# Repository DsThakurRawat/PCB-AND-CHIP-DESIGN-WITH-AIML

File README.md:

# PCB-AI: Autonomous AI-Assisted Electronics & KiCad Engineering System

An end-to-end open-source pipeline for programmatic circuit synthesis, schematic capture, SPICE simulation, PCB layout, automated routing, and manufacturing exports using **KiCad 9**, **ngspice**, **FreeRouting**, **InteractiveHtmlBom**, **OpenCode**, and **Antigravity**.

---

## 🚀 Architecture & Core Pipelines

```
                     ┌───────────────────────────────┐
                     │   Structured Circuit Spec     │
                     │         (JSON / AI)           │
                     └───────────────┬───────────────┘
                                     │
           ┌─────────────────────────┴─────────────────────────┐
           ▼                                                   ▼
┌───────────────────────┐                           ┌─────────────────────┐
│  SPICE Simulator      │                           │  Schematic Builder  │
│  (ngspice 45.2)       │                           │  (kicad_sch_api)    │
└──────────┬────────────┘                           └──────────┬──────────┘
           │                                                   │
           ▼ (AC / Transient Plots)                            ▼ (.kicad_sch)
┌───────────────────────┐                           ┌─────────────────────┐
│ Waveform Analysis     │                           │ Automated ERC Check │
│ (Bode / Transient)    │                           │ (0 Violations)      │
└───────────────────────┘                           └──────────┬──────────┘
                                                               │
                                                               ▼ (.kicad_pcb)
                                                    ┌─────────────────────┐
                                                    │   PCB Layout Engine │
                                                    │   (pcbnew Python)   │
                                                    └──────────┬──────────┘
                                                               │
           ┌───────────────────────────────────────────────────┴───────────────────────────────────────┐
           ▼                                                   ▼                                       ▼
┌───────────────────────┐                           ┌─────────────────────┐                 ┌─────────────────────┐
│  FreeRouting Engine   │                           │  DRC Validator      │                 │ Manufacturing Pack  │
│  (Java 25 + DSN/SES)  │                           │  (--exit-code)      │                 │ Gerbers, Drill, BOM │
└───────────────────────┘                           └─────────────────────┘                 └──────────┬──────────┘
                                                                                                       │
                                                    ┌──────────────────────────────────────────────────┴──────────┐
                                                    ▼                                                             ▼
                                     ┌─────────────────────────────┐                               ┌─────────────────────────────┐
                                     │  Interactive HTML BOM       │                               │  3D Raytrace Render         │
                                     │  (InteractiveHtmlBom)       │                               │  (Perspective + Shaders)    │
                                     └─────────────────────────────┘                               └─────────────────────────────┘
```

---

## 🛠️ Toolchain & Installed Components

| Tool | Version | Purpose |
| :--- | :---: | :--- |
| **KiCad Suite** | 9.0.8 | Headless CLI automation & interactive visual design |
| **pcbnew** | 9.0.8 bindings | Direct programmatic PCB inspection & manipulation |
| **ngspice** | 45.2 | Circuit simulation (AC Bode frequency sweeps, Transient, DC) |
| **OpenJDK** | 25.0.4.1 | Java runtime for automated routing engine |
| **FreeRouting** | 2.5.0 | Specctra DSN/SES automated trace router |
| **InteractiveHtmlBom** | Latest | Self-contained visual HTML BOM for prototype assembly |
| **kicad_sch_api** | 0.5.5 | Programmatic schematic generation and wiring |
| **shapely** | 2.2.0 | 2D computational geometry and board outline math |
| **OpenCode MCP** | Active | Paired with `opencode/glm-5.3-flash-free` |
| **Antigravity MCP** | Active | Configured with 80+ native KiCad tools in `mcp_config.json` |

---

## 📁 Repository Structure

```
PCBDESIGN/
├── pcb_engine/
│   ├── circuit_spec.py      # Pydantic schema for structured circuit definitions
│   ├── sch_builder.py       # Programmatic .kicad_sch generator & auto-wiring
│   ├── pcb_builder.py       # Programmatic .kicad_pcb layout & footprint generator
│   └── simulator.py         # ngspice AC/transient simulator & matplotlib plotter
│
├── scripts/
│   ├── validate_design.py   # Automated ERC & DRC runner (--exit-code-violations)
│   ├── generate_ibom.py     # Interactive HTML BOM generator
│   ├── render_3d.py         # Altium-style 3D raytrace renderer
│   ├── autoroute.py         # Standalone Freerouting CLI runner
│   ├── export_manufacturing.py # Complete Gerber, drill, pos, PDF, 3D, and iBOM packager
│   └── run_all_benchmarks.sh   # Master benchmark verification suite
│
├── reference_circuits/
│   ├── 01_ldo_power_supply/ # 3.3V Linear Voltage Regulator Module
│   │   ├── spec.json        # Circuit specification
│   │   ├── ldo_power_supply.kicad_sch
│   │   ├── ldo_power_supply.kicad_pcb
│   │   ├── simulation_transient.png
│   │   └── manufacturing/   # Gerbers ZIP, drill, pos CSV, PDF, ibom.html, 3d.png
│   │
│   └── 02_sallen_key_filter/# 2nd-Order Sallen-Key Active Low-Pass Filter (1 kHz)
│       ├── spec.json        # Circuit specification
│       ├── sallen_key_filter.kicad_sch
│       ├── sallen_key_filter.kicad_pcb
│       ├── simulation_bode.png
│       └── manufacturing/   # Gerbers ZIP, drill, pos CSV, PDF, ibom.html, 3d.png
│
├── ne555_led_blinker/        # Single-Layer Astable 1Hz LED Blinker (DIP-8, 48x36mm)
│   ├── spec.json            # Circuit definition
│   ├── ne555_led_blinker.kicad_sch
│   ├── ne555_led_blinker.kicad_pcb  # 100% single-layer routed on F.Cu (0 vias, 0 DRC violations)
│   ├── ne555_simulation_transient.png
│   └── manufacturing/       # Gerbers ZIP, drill, pos CSV, PDF, ibom.html, 3d.png
│
├── docs/
│   ├── ENGINEERING_RULES_AND_LESSONS.md # Complete rules, failure modes & decisions log
│   └── mcp_vs_scripting_benchmark.md    # KiCad MCP vs scripting comparison
│
├── demo_board/              # Test project used for live GUI tracking & MCP verification
└── README.md
```

---

## ⚡ Quick Start & Commands

### 1. Run Complete Benchmark Suite
```bash
./scripts/run_all_benchmarks.sh
```

### 2. Validate Any Schematic or Board
```bash
python3 scripts/validate_design.py --sch <path_to_sch> --pcb <path_to_pcb>
```

### 3. Generate Interactive HTML BOM
```bash
python3 scripts/generate_ibom.py <path_to_pcb> [output_dir]
```

### 4. Generate Altium-Style 3D Render
```bash
python3 scripts/render_3d.py <path_to_pcb> [output_image.png]
```

### 5. Package Complete Manufacturing Archive (Gerbers + Drill + iBOM + 3D)
```bash
python3 scripts/export_manufacturing.py <path_to_pcb> [output_dir]
```

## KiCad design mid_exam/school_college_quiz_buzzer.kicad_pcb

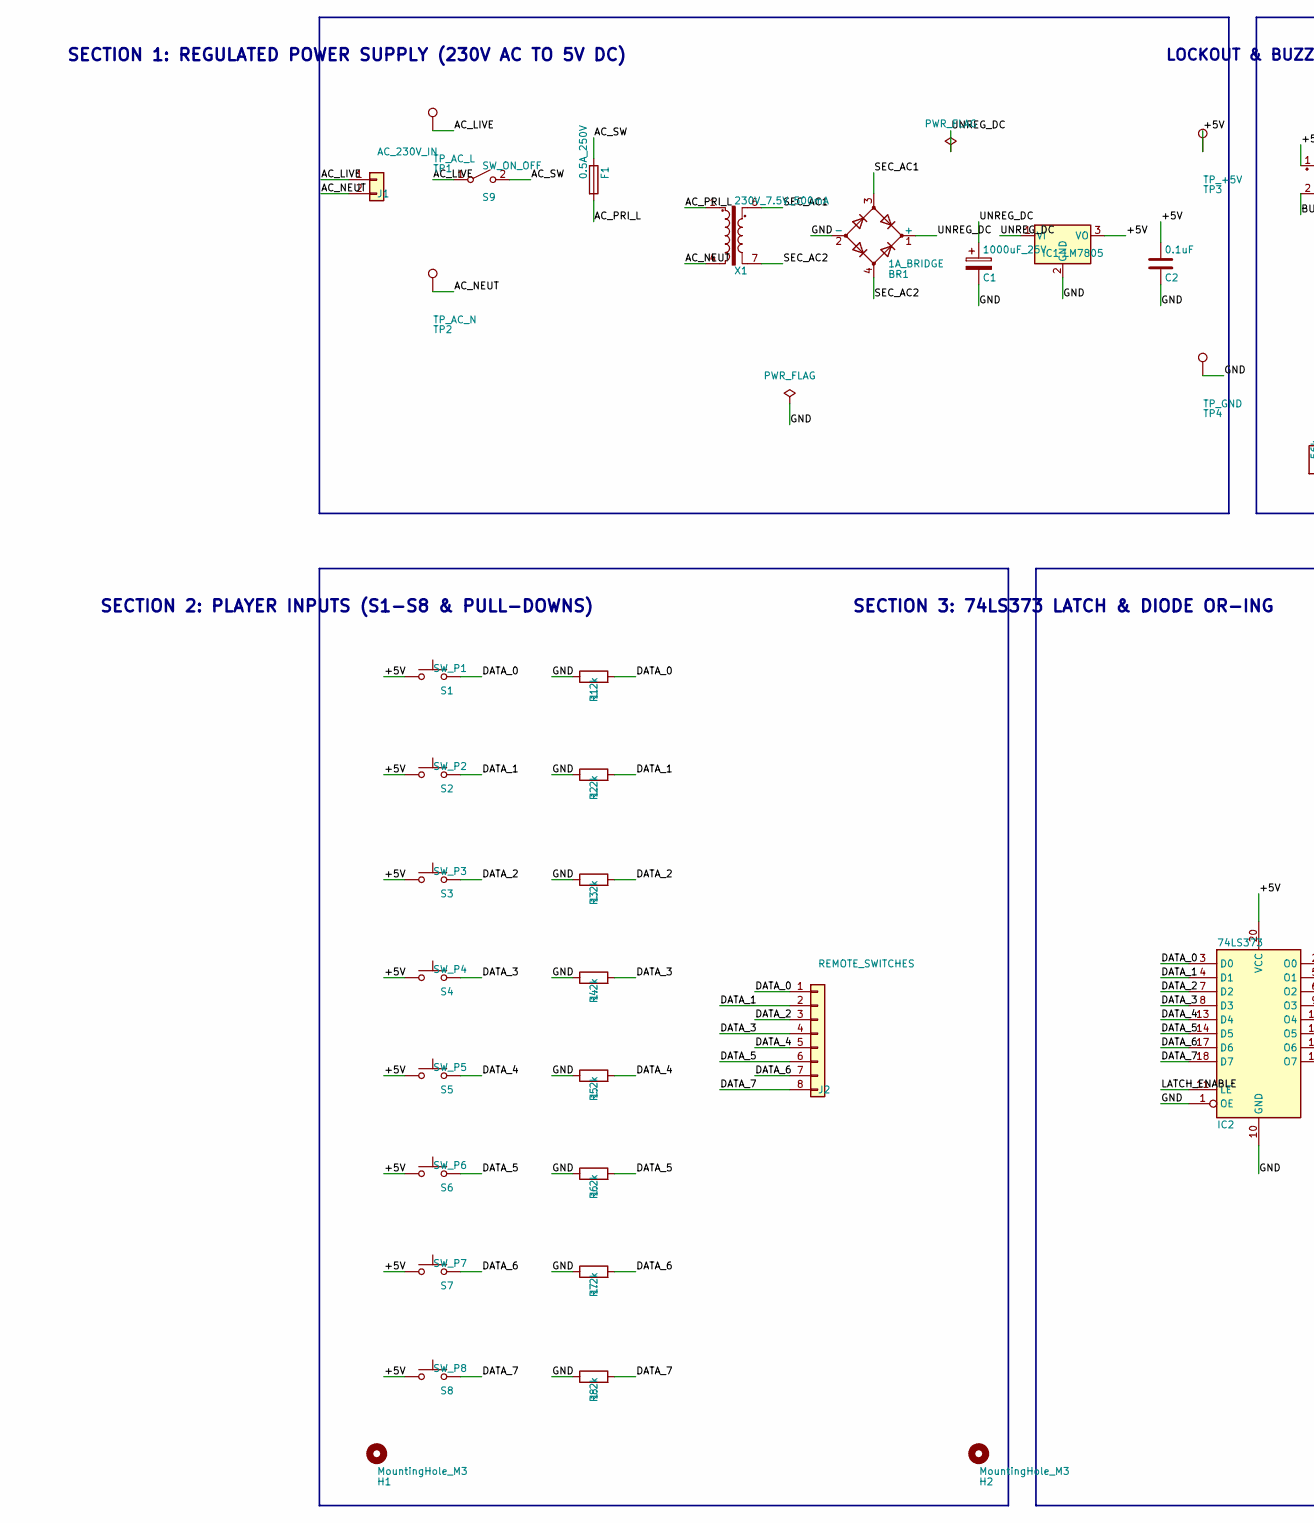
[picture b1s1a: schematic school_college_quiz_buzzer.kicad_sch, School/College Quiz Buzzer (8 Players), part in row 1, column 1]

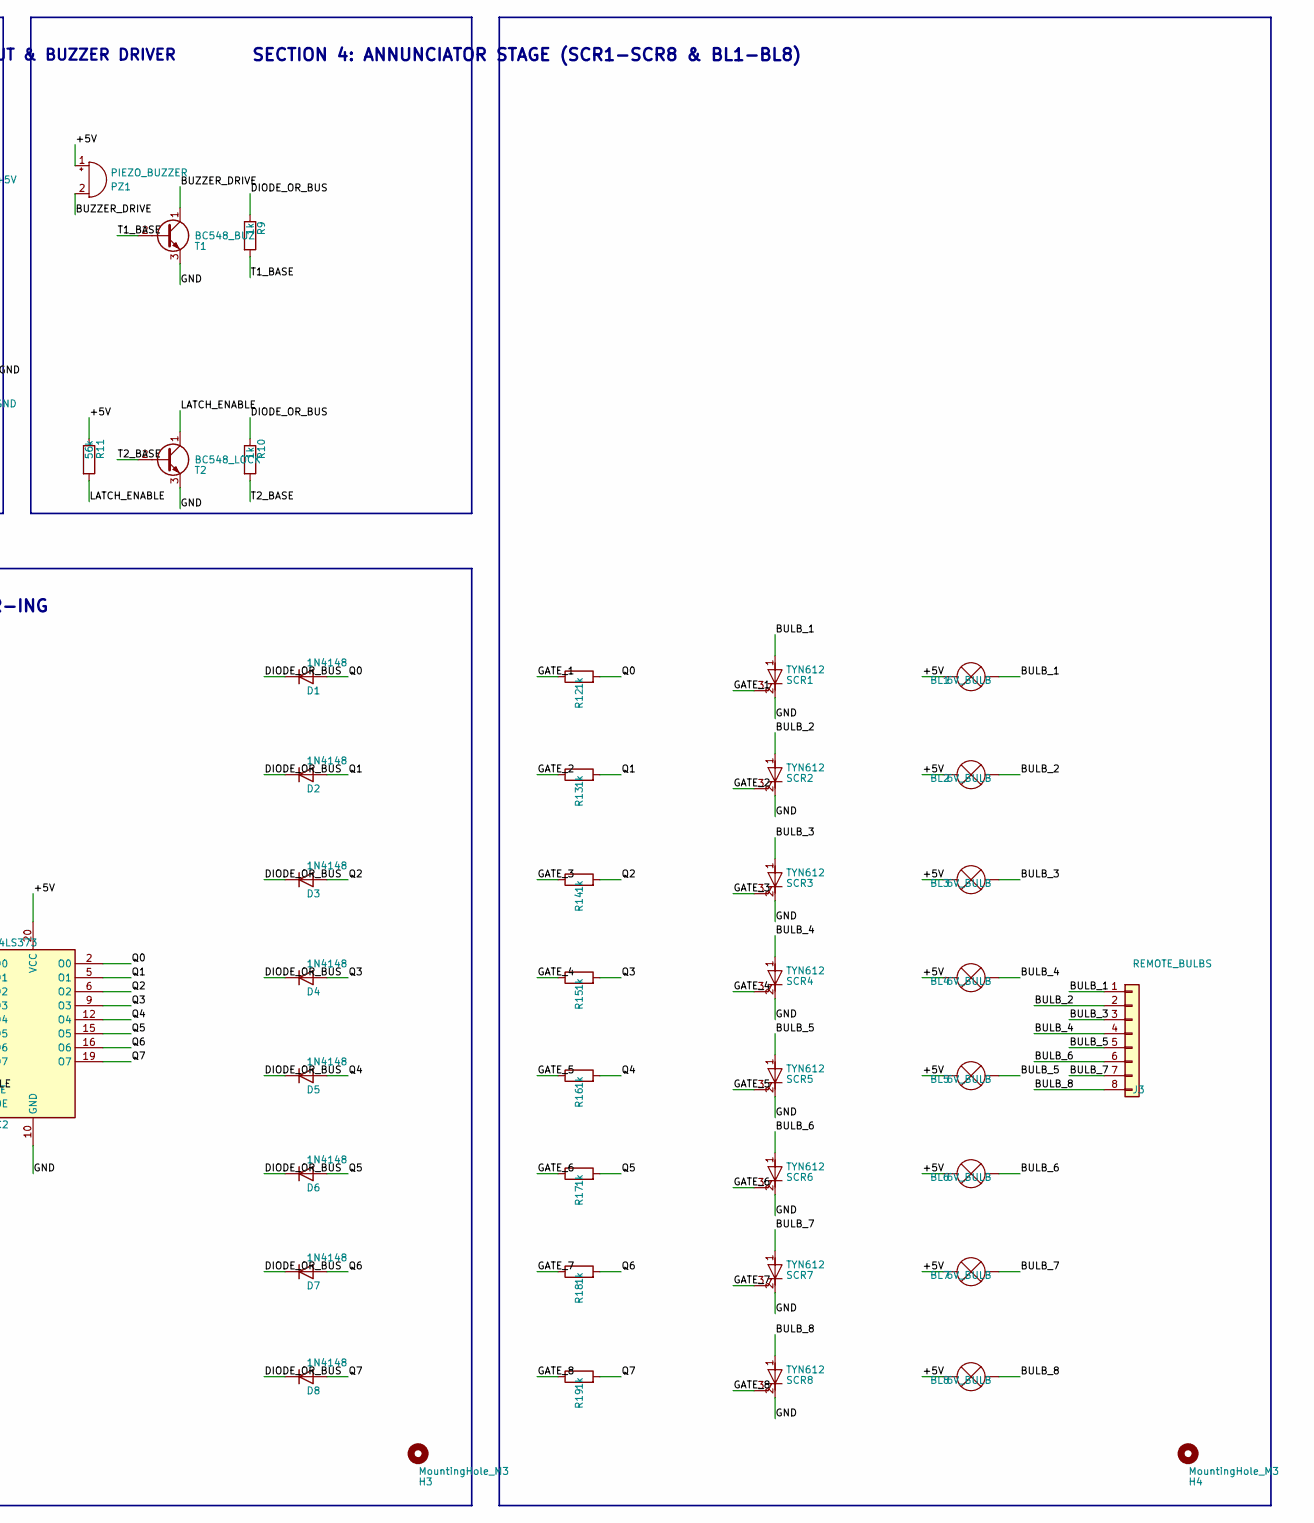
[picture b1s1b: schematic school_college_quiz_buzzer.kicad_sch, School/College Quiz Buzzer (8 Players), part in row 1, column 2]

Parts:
BL1, BL2, BL3, BL4, BL5, BL6, BL7, BL8: 6V_BULB; PinHeader_1x02_P2.54mm_Vertical
BR1: 1A_BRIDGE; Diode_Bridge_Round_D9.0mm
C1: 1000uF_25V; CP_Radial_D10.0mm_P5.00mm
C2: 0.1uF; C_Disc_D4.3mm_W1.9mm_P5.00mm
D1, D2, D3, D4, D5, D6, D7, D8: 1N4148; D_DO-35_SOD27_P7.62mm_Horizontal
F1: 0.5A_250V; Fuseholder_Cylinder-5x20mm_Schurter_0031_8201_Horizontal_Op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
H1, H2, H3, H4: MountingHole_M3; MountingHole_3.2mm_M3
IC1: LM7805; TO-220-3_Vertical
IC2: 74LS373; DIP-20_W7.62mm
J1: AC_230V_IN; TerminalBlock_Phoenix_MPT-0,5-2-2.54_1x02_P2.54mm_Horizontal
J2: REMOTE_SWITCHES; PinHeader_1x08_P2.54mm_Vertical
J3: REMOTE_BULBS; PinHeader_1x08_P2.54mm_Vertical
PZ1: PIEZO_BUZZER; Buzzer_12x9.5RM7.6
R1, R2, R3, R4, R5, R6, R7, R8: 1.2k; R_Axial_DIN0207_L6.3mm_D2.5mm_P7.62mm_Horizontal
R9, R10, R12, R13, R14, R15, R16, R17, R18, R19: 1k; R_Axial_DIN0207_L6.3mm_D2.5mm_P7.62mm_Horizontal
R11: 56k; R_Axial_DIN0207_L6.3mm_D2.5mm_P7.62mm_Horizontal
S1: SW_P1; SW_PUSH_6mm
S2: SW_P2; SW_PUSH_6mm
S3: SW_P3; SW_PUSH_6mm
S4: SW_P4; SW_PUSH_6mm
S5: SW_P5; SW_PUSH_6mm
S6: SW_P6; SW_PUSH_6mm
S7: SW_P7; SW_PUSH_6mm
S8: SW_P8; SW_PUSH_6mm
S9: SW_ON_OFF; SW_Slide_SPDT_Angled_CK_OS102011MA1Q
SCR1, SCR2, SCR3, SCR4, SCR5, SCR6, SCR7, SCR8: TYN612; TO-220-3_Vertical
T1: BC548_BUZ; TO-92_Inline
T2: BC548_LOCK; TO-92_Inline
TP1: TP_AC_L; TestPoint_THTPad_D1.5mm_Drill0.7mm
TP2: TP_AC_N; TestPoint_THTPad_D1.5mm_Drill0.7mm
TP3: TP_+5V; TestPoint_THTPad_D1.5mm_Drill0.7mm
TP4: TP_GND; TestPoint_THTPad_D1.5mm_Drill0.7mm
X1: 230V_7.5V_500mA; Transformer_Breve_TEZ-22x24

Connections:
/+5V: BL1.2 (+), BL2.2 (+), BL3.2 (+), BL4.2 (+), BL5.2 (+), BL6.2 (+), BL7.2 (+), BL8.2 (+), C2.1, IC1.3 (VO), IC2.20 (VCC), PZ1.1 (+), R11.1, S1.1, S2.1, S3.1, S4.1, S5.1, S6.1, S7.1, S8.1, TP3.1
/AC_LIVE: J1.1, S9.1 (A), TP1.1
/AC_NEUT: J1.2, TP2.1, X1.4
/AC_PRI_L: F1.2, X1.1
/AC_SW: F1.1, S9.2 (B)
/BULB_1: BL1.1 (-), J3.1, SCR1.1 (A)
/BULB_2: BL2.1 (-), J3.2, SCR2.1 (A)
/BULB_3: BL3.1 (-), J3.3, SCR3.1 (A)
/BULB_4: BL4.1 (-), J3.4, SCR4.1 (A)
/BULB_5: BL5.1 (-), J3.5, SCR5.1 (A)
/BULB_6: BL6.1 (-), J3.6, SCR6.1 (A)
/BULB_7: BL7.1 (-), J3.7, SCR7.1 (A)
/BULB_8: BL8.1 (-), J3.8, SCR8.1 (A)
/BUZZER_DRIVE: PZ1.2 (-), T1.1 (C)
/DATA_0: IC2.3 (D0), J2.1, R1.2, S1.2
/DATA_1: IC2.4 (D1), J2.2, R2.2, S2.2
/DATA_2: IC2.7 (D2), J2.3, R3.2, S3.2
/DATA_3: IC2.8 (D3), J2.4, R4.2, S4.2
/DATA_4: IC2.13 (D4), J2.5, R5.2, S5.2
/DATA_5: IC2.14 (D5), J2.6, R6.2, S6.2
/DATA_6: IC2.17 (D6), J2.7, R7.2, S7.2
/DATA_7: IC2.18 (D7), J2.8, R8.2, S8.2
/DIODE_OR_BUS: D1.1 (K), D2.1 (K), D3.1 (K), D4.1 (K), D5.1 (K), D6.1 (K), D7.1 (K), D8.1 (K), R9.1, R10.1
/GATE_1: R12.1, SCR1.3 (G)
/GATE_2: R13.1, SCR2.3 (G)
/GATE_3: R14.1, SCR3.3 (G)
/GATE_4: R15.1, SCR4.3 (G)
/GATE_5: R16.1, SCR5.3 (G)
/GATE_6: R17.1, SCR6.3 (G)
/GATE_7: R18.1, SCR7.3 (G)
/GATE_8: R19.1, SCR8.3 (G)
/GND: BR1.2 (-), C1.2, C2.2, IC1.2 (GND), IC2.1 (OE), IC2.10 (GND), R1.1, R2.1, R3.1, R4.1, R5.1, R6.1, R7.1, R8.1, SCR1.2 (K), SCR2.2 (K), SCR3.2 (K), SCR4.2 (K), SCR5.2 (K), SCR6.2 (K), SCR7.2 (K), SCR8.2 (K), T1.3 (E), T2.3 (E), TP4.1
/LATCH_ENABLE: IC2.11 (LE), R11.2, T2.1 (C)
/Q0: D1.2 (A), IC2.2 (O0), R12.2
/Q1: D2.2 (A), IC2.5 (O1), R13.2
/Q2: D3.2 (A), IC2.6 (O2), R14.2
/Q3: D4.2 (A), IC2.9 (O3), R15.2
/Q4: D5.2 (A), IC2.12 (O4), R16.2
/Q5: D6.2 (A), IC2.15 (O5), R17.2
/Q6: D7.2 (A), IC2.16 (O6), R18.2
/Q7: D8.2 (A), IC2.19 (O7), R19.2
/SEC_AC1: BR1.3, X1.6
/SEC_AC2: BR1.4, X1.7
/T1_BASE: R9.2, T1.2 (B)
/T2_BASE: R10.2, T2.2 (B)
/UNREG_DC: BR1.1 (+), C1.1, IC1.1 (VI)

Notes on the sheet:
SECTION 1: REGULATED POWER SUPPLY (230V AC TO 5V DC)
SECTION 2: PLAYER INPUTS (S1-S8 & PULL-DOWNS)
SECTION 3: 74LS373 LATCH & DIODE OR-ING
LOCKOUT & BUZZER DRIVER
SECTION 4: ANNUNCIATOR STAGE (SCR1-SCR8 & BL1-BL8)

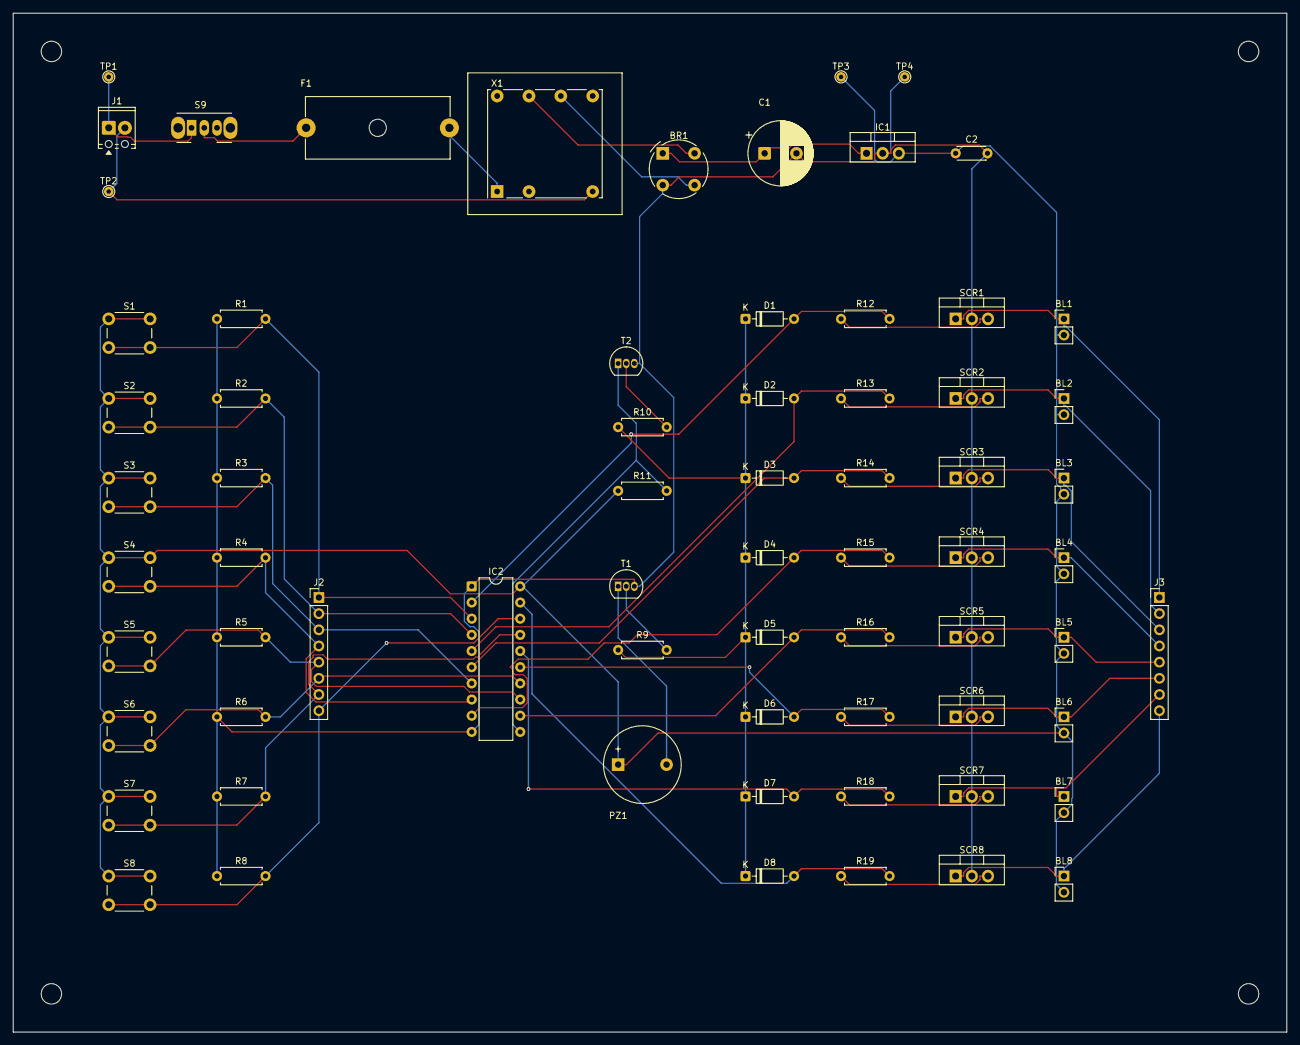
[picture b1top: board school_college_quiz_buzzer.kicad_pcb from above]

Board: 2 copper layers, 200.0 x 160.0 mm, 73 parts (0 on the bottom side), 46 nets.

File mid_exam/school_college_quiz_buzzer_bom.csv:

"Refs","Value","Footprint","Qty","DNP"
"BL1","6V_BULB","Connector_PinHeader_2.54mm:PinHeader_1x02_P2.54mm_Vertical","1",""
"BL2","6V_BULB","Connector_PinHeader_2.54mm:PinHeader_1x02_P2.54mm_Vertical","1",""
"BL3","6V_BULB","Connector_PinHeader_2.54mm:PinHeader_1x02_P2.54mm_Vertical","1",""
"BL4","6V_BULB","Connector_PinHeader_2.54mm:PinHeader_1x02_P2.54mm_Vertical","1",""
"BL5","6V_BULB","Connector_PinHeader_2.54mm:PinHeader_1x02_P2.54mm_Vertical","1",""
"BL6","6V_BULB","Connector_PinHeader_2.54mm:PinHeader_1x02_P2.54mm_Vertical","1",""
"BL7","6V_BULB","Connector_PinHeader_2.54mm:PinHeader_1x02_P2.54mm_Vertical","1",""
"BL8","6V_BULB","Connector_PinHeader_2.54mm:PinHeader_1x02_P2.54mm_Vertical","1",""
"BR1","1A_BRIDGE","Diode_THT:Diode_Bridge_Round_D9.0mm","1",""
"C1","1000uF_25V","Capacitor_THT:CP_Radial_D10.0mm_P5.00mm","1",""
"C2","0.1uF","Capacitor_THT:C_Disc_D4.3mm_W1.9mm_P5.00mm","1",""
"D1","1N4148","Diode_THT:D_DO-35_SOD27_P7.62mm_Horizontal","1",""
"D2","1N4148","Diode_THT:D_DO-35_SOD27_P7.62mm_Horizontal","1",""
"D3","1N4148","Diode_THT:D_DO-35_SOD27_P7.62mm_Horizontal","1",""
"D4","1N4148","Diode_THT:D_DO-35_SOD27_P7.62mm_Horizontal","1",""
"D5","1N4148","Diode_THT:D_DO-35_SOD27_P7.62mm_Horizontal","1",""
"D6","1N4148","Diode_THT:D_DO-35_SOD27_P7.62mm_Horizontal","1",""
"D7","1N4148","Diode_THT:D_DO-35_SOD27_P7.62mm_Horizontal","1",""
"D8","1N4148","Diode_THT:D_DO-35_SOD27_P7.62mm_Horizontal","1",""
"F1","0.5A_250V","Fuse:Fuseholder_Cylinder-5x20mm_Schurter_0031_8201_Horizontal_Open","1",""
"H1","MountingHole_M3","MountingHole:MountingHole_3.2mm_M3","1",""
"H2","MountingHole_M3","MountingHole:MountingHole_3.2mm_M3","1",""
"H3","MountingHole_M3","MountingHole:MountingHole_3.2mm_M3","1",""
"H4","MountingHole_M3","MountingHole:MountingHole_3.2mm_M3","1",""
"IC1","LM7805","Package_TO_SOT_THT:TO-220-3_Vertical","1",""
"IC2","74LS373","Package_DIP:DIP-20_W7.62mm","1",""
"J1","AC_230V_IN","TerminalBlock_Phoenix:TerminalBlock_Phoenix_MPT-0,5-2-2.54_1x02_P2.54mm_Horizontal","1",""
"J2","REMOTE_SWITCHES","Connector_PinHeader_2.54mm:PinHeader_1x08_P2.54mm_Vertical","1",""
"J3","REMOTE_BULBS","Connector_PinHeader_2.54mm:PinHeader_1x08_P2.54mm_Vertical","1",""
"PZ1","PIEZO_BUZZER","Buzzer_Beeper:Buzzer_12x9.5RM7.6","1",""
"R1","1.2k","Resistor_THT:R_Axial_DIN0207_L6.3mm_D2.5mm_P7.62mm_Horizontal","1",""
"R2","1.2k","Resistor_THT:R_Axial_DIN0207_L6.3mm_D2.5mm_P7.62mm_Horizontal","1",""
"R3","1.2k","Resistor_THT:R_Axial_DIN0207_L6.3mm_D2.5mm_P7.62mm_Horizontal","1",""
"R4","1.2k","Resistor_THT:R_Axial_DIN0207_L6.3mm_D2.5mm_P7.62mm_Horizontal","1",""
"R5","1.2k","Resistor_THT:R_Axial_DIN0207_L6.3mm_D2.5mm_P7.62mm_Horizontal","1",""
"R6","1.2k","Resistor_THT:R_Axial_DIN0207_L6.3mm_D2.5mm_P7.62mm_Horizontal","1",""
"R7","1.2k","Resistor_THT:R_Axial_DIN0207_L6.3mm_D2.5mm_P7.62mm_Horizontal","1",""
"R8","1.2k","Resistor_THT:R_Axial_DIN0207_L6.3mm_D2.5mm_P7.62mm_Horizontal","1",""
"R9","1k","Resistor_THT:R_Axial_DIN0207_L6.3mm_D2.5mm_P7.62mm_Horizontal","1",""
"R10","1k","Resistor_THT:R_Axial_DIN0207_L6.3mm_D2.5mm_P7.62mm_Horizontal","1",""
"R11","56k","Resistor_THT:R_Axial_DIN0207_L6.3mm_D2.5mm_P7.62mm_Horizontal","1",""
"R12","1k","Resistor_THT:R_Axial_DIN0207_L6.3mm_D2.5mm_P7.62mm_Horizontal","1",""
"R13","1k","Resistor_THT:R_Axial_DIN0207_L6.3mm_D2.5mm_P7.62mm_Horizontal","1",""
"R14","1k","Resistor_THT:R_Axial_DIN0207_L6.3mm_D2.5mm_P7.62mm_Horizontal","1",""
"R15","1k","Resistor_THT:R_Axial_DIN0207_L6.3mm_D2.5mm_P7.62mm_Horizontal","1",""
"R16","1k","Resistor_THT:R_Axial_DIN0207_L6.3mm_D2.5mm_P7.62mm_Horizontal","1",""
"R17","1k","Resistor_THT:R_Axial_DIN0207_L6.3mm_D2.5mm_P7.62mm_Horizontal","1",""
"R18","1k","Resistor_THT:R_Axial_DIN0207_L6.3mm_D2.5mm_P7.62mm_Horizontal","1",""
"R19","1k","Resistor_THT:R_Axial_DIN0207_L6.3mm_D2.5mm_P7.62mm_Horizontal","1",""
"S1","SW_P1","Button_Switch_THT:SW_PUSH_6mm","1",""
"S2","SW_P2","Button_Switch_THT:SW_PUSH_6mm","1",""
"S3","SW_P3","Button_Switch_THT:SW_PUSH_6mm","1",""
"S4","SW_P4","Button_Switch_THT:SW_PUSH_6mm","1",""
"S5","SW_P5","Button_Switch_THT:SW_PUSH_6mm","1",""
"S6","SW_P6","Button_Switch_THT:SW_PUSH_6mm","1",""
"S7","SW_P7","Button_Switch_THT:SW_PUSH_6mm","1",""
"S8","SW_P8","Button_Switch_THT:SW_PUSH_6mm","1",""
"S9","SW_ON_OFF","Button_Switch_THT:SW_Slide_SPDT_Angled_CK_OS102011MA1Q","1",""
"SCR1","TYN612","Package_TO_SOT_THT:TO-220-3_Vertical","1",""
"SCR2","TYN612","Package_TO_SOT_THT:TO-220-3_Vertical","1",""
"SCR3","TYN612","Package_TO_SOT_THT:TO-220-3_Vertical","1",""
"SCR4","TYN612","Package_TO_SOT_THT:TO-220-3_Vertical","1",""
"SCR5","TYN612","Package_TO_SOT_THT:TO-220-3_Vertical","1",""
"SCR6","TYN612","Package_TO_SOT_THT:TO-220-3_Vertical","1",""
"SCR7","TYN612","Package_TO_SOT_THT:TO-220-3_Vertical","1",""
"SCR8","TYN612","Package_TO_SOT_THT:TO-220-3_Vertical","1",""
"T1","BC548_BUZ","Package_TO_SOT_THT:TO-92_Inline","1",""
"T2","BC548_LOCK","Package_TO_SOT_THT:TO-92_Inline","1",""
"TP1","TP_AC_L","TestPoint:TestPoint_THTPad_D1.5mm_Drill0.7mm","1",""
"TP2","TP_AC_N","TestPoint:TestPoint_THTPad_D1.5mm_Drill0.7mm","1",""
"TP3","TP_+5V","TestPoint:TestPoint_THTPad_D1.5mm_Drill0.7mm","1",""
"TP4","TP_GND","TestPoint:TestPoint_THTPad_D1.5mm_Drill0.7mm","1",""
"X1","230V_7.5V_500mA","Transformer_THT:Transformer_Breve_TEZ-22x24","1",""

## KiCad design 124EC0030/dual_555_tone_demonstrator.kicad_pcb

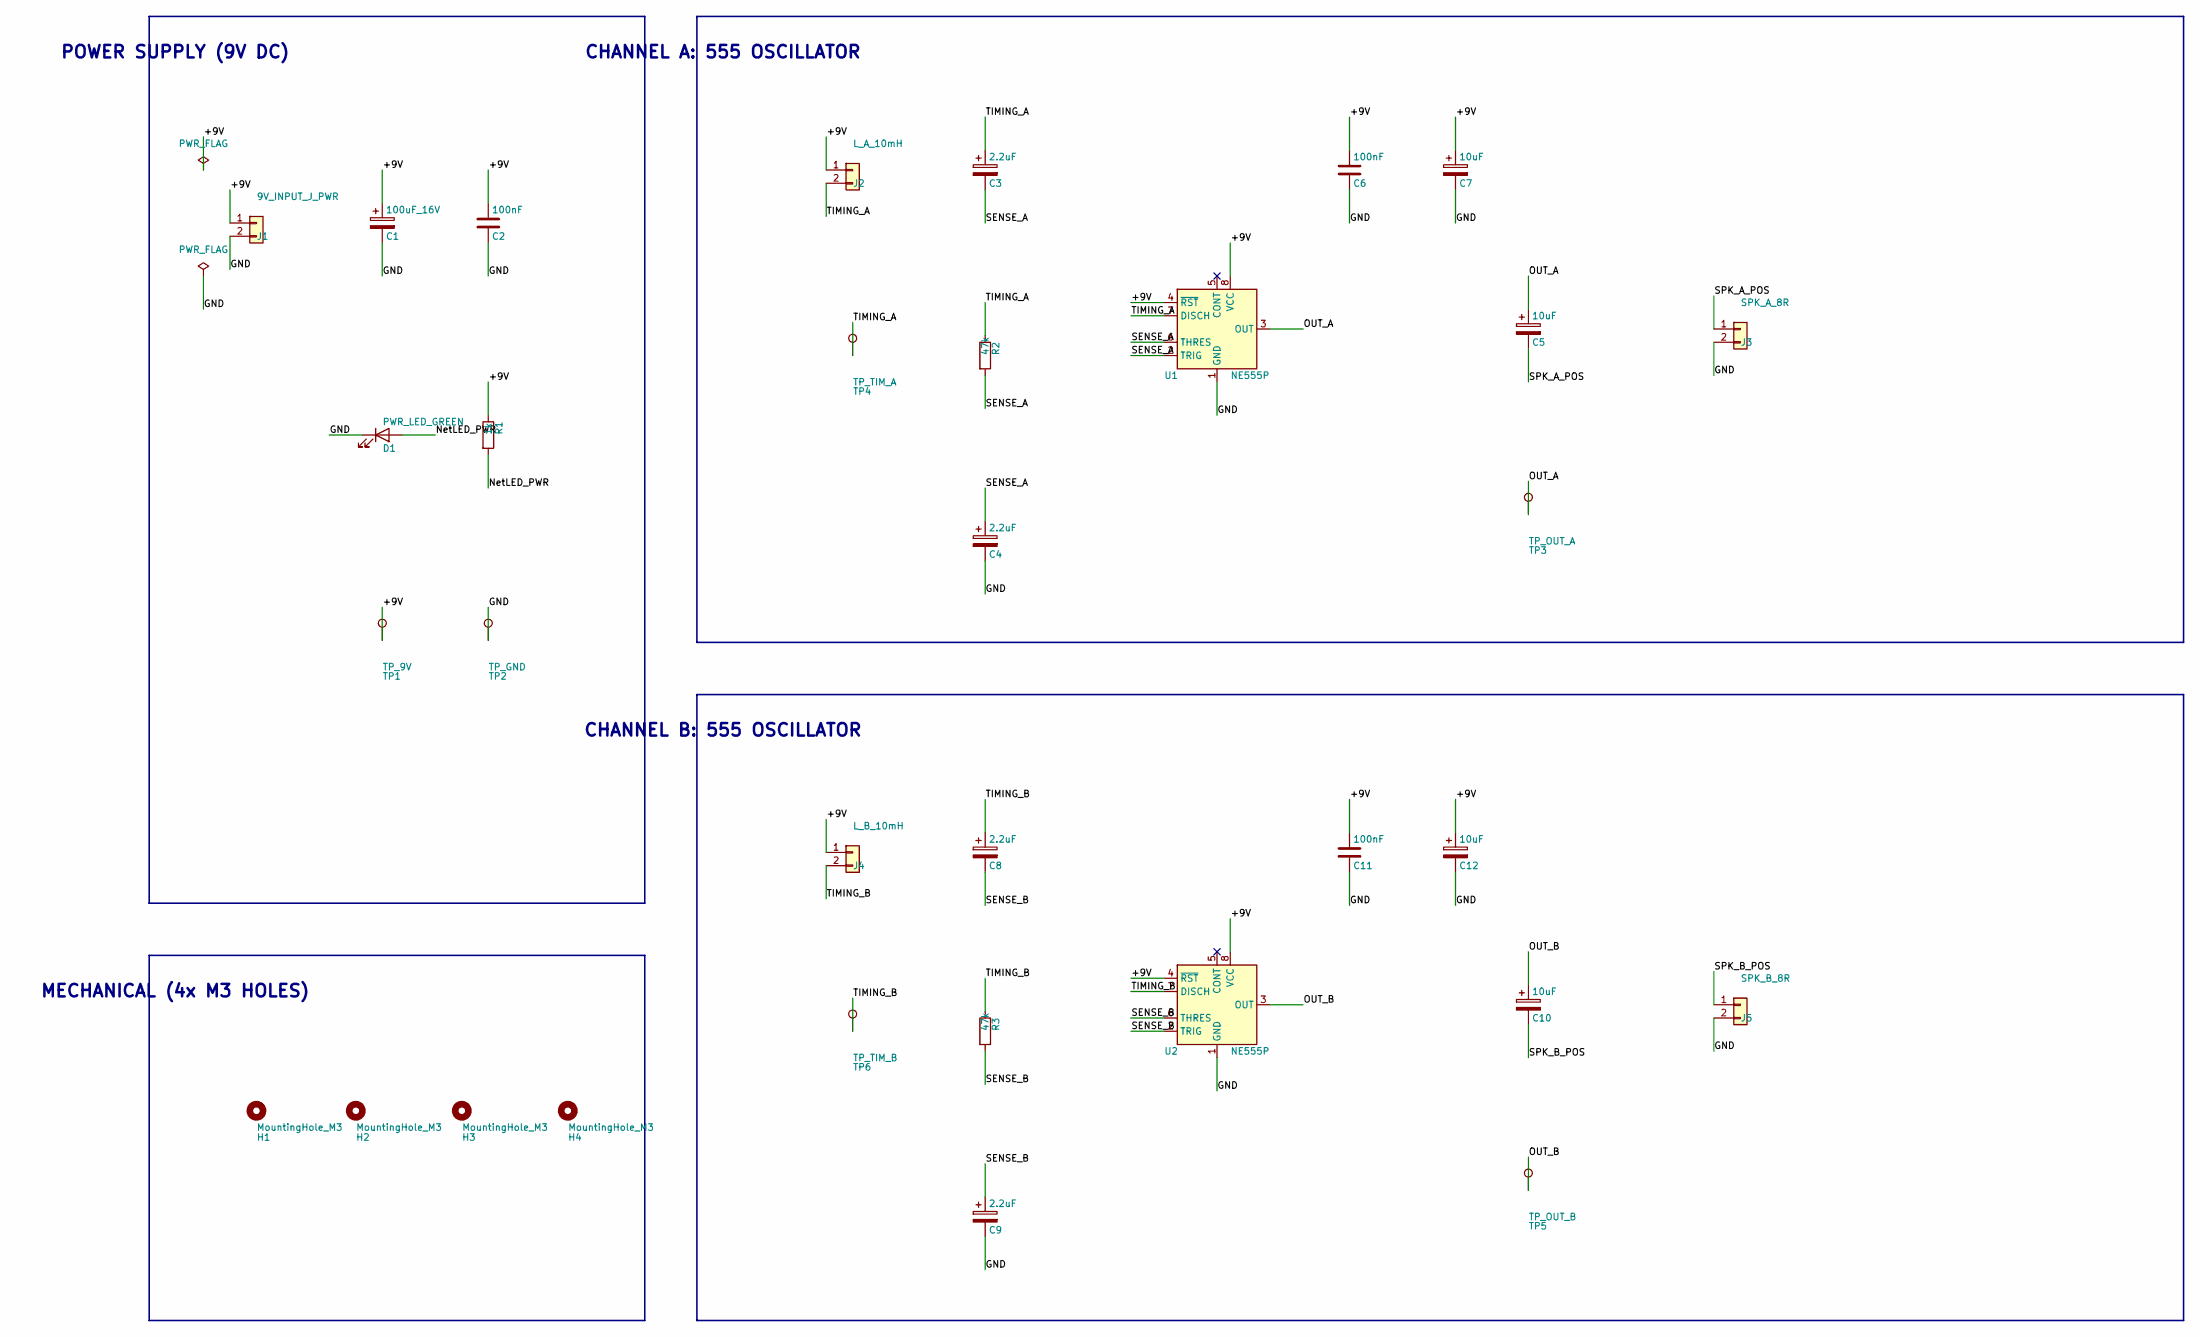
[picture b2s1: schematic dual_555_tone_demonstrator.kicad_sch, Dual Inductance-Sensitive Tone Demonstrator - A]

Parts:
C1: 100uF_16V; CP_Radial_D6.3mm_P2.50mm
C2, C6, C11: 100nF; C_Disc_D4.3mm_W1.9mm_P5.00mm
C3, C4, C8, C9: 2.2uF; CP_Radial_D5.0mm_P2.00mm
C5, C7, C10, C12: 10uF; CP_Radial_D5.0mm_P2.00mm
D1: PWR_LED_GREEN; LED_D3.0mm
H1, H2, H3, H4: MountingHole_M3; MountingHole_3.2mm_M3
J1: 9V_INPUT_J_PWR; TerminalBlock_Phoenix_MPT-0,5-2-2.54_1x02_P2.54mm_Horizontal
J2: L_A_10mH; PinHeader_1x02_P2.54mm_Vertical
J3: SPK_A_8R; PinHeader_1x02_P2.54mm_Vertical
J4: L_B_10mH; PinHeader_1x02_P2.54mm_Vertical
J5: SPK_B_8R; PinHeader_1x02_P2.54mm_Vertical
R1: 1k; R_Axial_DIN0207_L6.3mm_D2.5mm_P7.62mm_Horizontal
R2, R3: 47k; R_Axial_DIN0207_L6.3mm_D2.5mm_P7.62mm_Horizontal
TP1: TP_9V; TestPoint_THTPad_D1.5mm_Drill0.7mm
TP2: TP_GND; TestPoint_THTPad_D1.5mm_Drill0.7mm
TP3: TP_OUT_A; TestPoint_THTPad_D1.5mm_Drill0.7mm
TP4: TP_TIM_A; TestPoint_THTPad_D1.5mm_Drill0.7mm
TP5: TP_OUT_B; TestPoint_THTPad_D1.5mm_Drill0.7mm
TP6: TP_TIM_B; TestPoint_THTPad_D1.5mm_Drill0.7mm
U1, U2: NE555P; DIP-8_W7.62mm

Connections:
/+9V: C1.1, C2.1, C6.1, C7.1, C11.1, C12.1, J1.1, J2.1, J4.1, R1.1, TP1.1, U1.4 (~RST), U1.8 (VCC), U2.4 (~RST), U2.8 (VCC)
/GND: C1.2, C2.2, C4.2, C6.2, C7.2, C9.2, C11.2, C12.2, D1.1 (K), J1.2, J3.2, J5.2, TP2.1, U1.1 (GND), U2.1 (GND)
/NetLED_PWR: D1.2 (A), R1.2
/OUT_A: C5.1, TP3.1, U1.3 (OUT)
/OUT_B: C10.1, TP5.1, U2.3 (OUT)
/SENSE_A: C3.2, C4.1, R2.2, U1.2 (TRIG), U1.6 (THRES)
/SENSE_B: C8.2, C9.1, R3.2, U2.2 (TRIG), U2.6 (THRES)
/SPK_A_POS: C5.2, J3.1
/SPK_B_POS: C10.2, J5.1
/TIMING_A: C3.1, J2.2, R2.1, TP4.1, U1.7 (DISCH)
/TIMING_B: C8.1, J4.2, R3.1, TP6.1, U2.7 (DISCH)

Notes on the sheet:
POWER SUPPLY (9V DC)
CHANNEL A: 555 OSCILLATOR
CHANNEL B: 555 OSCILLATOR
MECHANICAL (4x M3 HOLES)

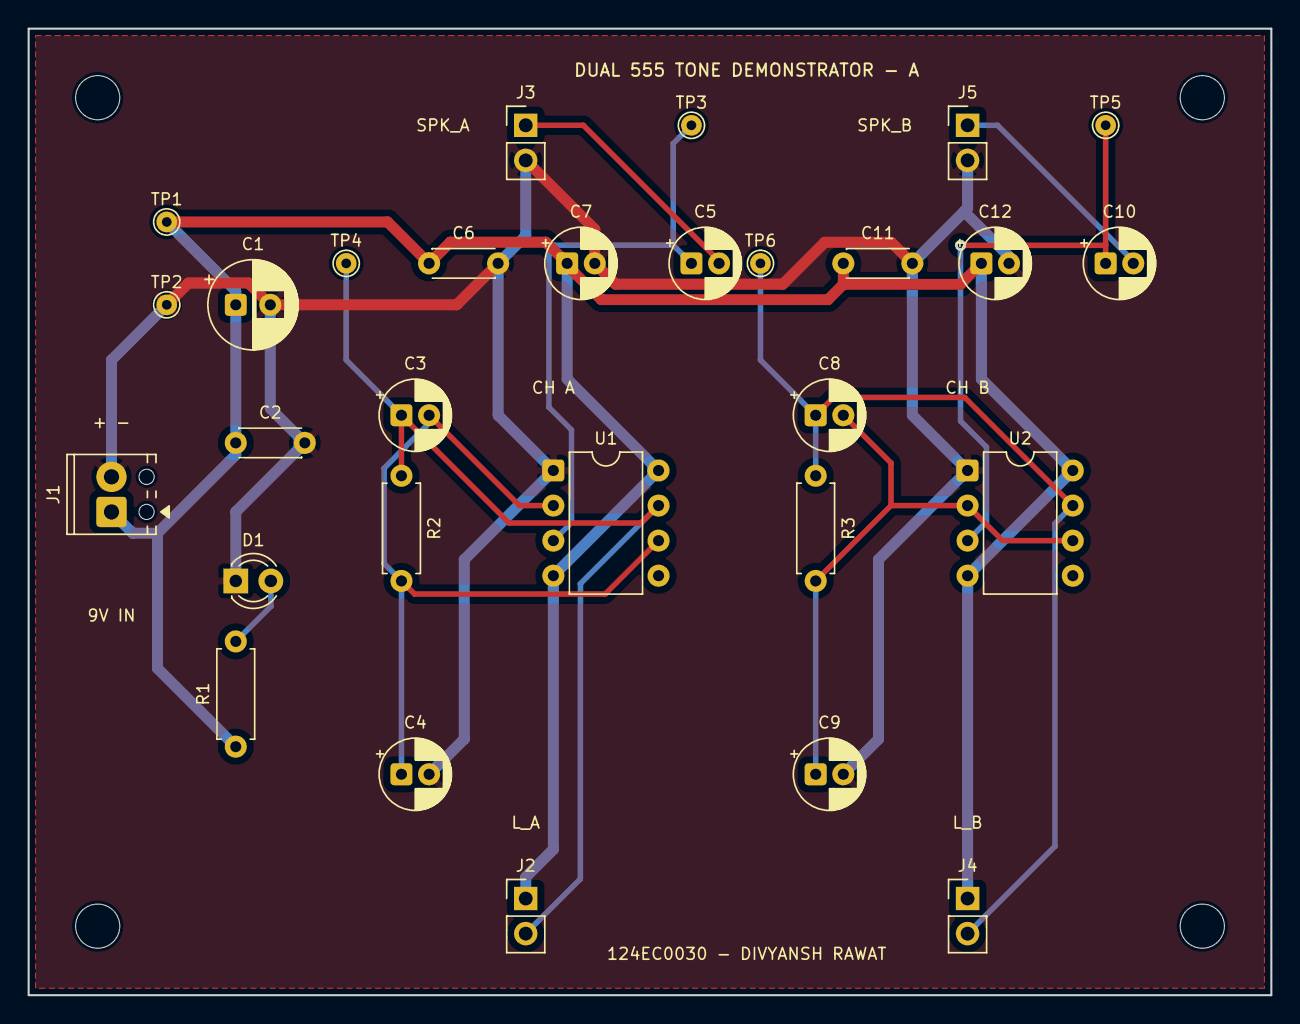
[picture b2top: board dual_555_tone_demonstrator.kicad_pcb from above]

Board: 2 copper layers, 90.0 x 70.0 mm, 33 parts (0 on the bottom side), 11 nets.

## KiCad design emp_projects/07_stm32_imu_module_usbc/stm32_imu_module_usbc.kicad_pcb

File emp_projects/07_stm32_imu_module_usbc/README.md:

# STM32-Based 6/9-DoF IMU Module with USB-C

## 📌 Project Overview
**Course Experiment:** Electronic Measurement Practices (EMP) — Project 07  
**PCB Architecture:** 4-Layer Controlled Impedance Design (SIG-GND-GND-SIG)  
**Primary Controller:** STM32F411CEU6 (ARM Cortex-M4 32-bit MCU with FPU, UFQFPN-48)  
**Motion Sensor:** TDK InvenSense MPU-6050 (6-Axis Gyroscope + Accelerometer, QFN-24)  
**Interface:** USB Type-C (Molex 217179-0001 Receptacle) with Dedicated ESD Protection  
**Deliverables Status:** Complete Turnkey Manufacturing Suite Verified (0 ERC Violations, 0 DRC Errors, 0 Unconnected Items, 0 Schematic Parity Mismatches)

---

## 🎯 Description & Operational Principles
Compact high-precision motion tracking inertial measurement unit featuring an STM32 MCU, 6-axis IMU, USB Type-C interface, ESD protection, and precision 3.3V low-dropout power conditioning.

### Key Features & Subsystems
- **Processor & Logic Core:** STM32F411CEU6 operating up to 100 MHz with 512 KB Flash, 128 KB SRAM, and 24 MHz external crystal oscillator.
- **Inertial Measurement Core:** MPU-6050 6-axis motion tracking sensor connected via dedicated I²C interface (`IMU_SCL` / `IMU_SDA` on PB8/PB9) with external hardware interrupt (`IMU_INT` on PB12).
- **USB Type-C Interfacing:** Molex 217179-0001 reversible connector with 5.1 kΩ CC pull-downs for automatic host detection, bidirectional USB 2.0 full-speed differential pair (`USB_D_P` / `USB_D_N`), and AQ3045-01ETG ESD protection diodes.
- **Power Architecture:** AMS1117-3.3V LDO regulator converting 5V USB VBUS to low-noise 3.3V system rail with bulk decoupling and filtered regulation networks.
- **Debug & Expansion:** No-legs Tag-Connect TC2030-NL SWD debugging interface and JST-GH SM06B-GHS-TB 6-pin auxiliary sensor expansion header.

---

## 🛠️ Bill of Materials (BOM Summary)

| Reference | Component Value | Package / Footprint | Description | Qty |
|:---:|:---:|:---:|:---|:---:|
| **U1** | AMS1117-3.3 | SOT-223 | 1A Low-Dropout Linear Voltage Regulator (5V to 3.3V) | 1 |
| **U2** | STM32F411CEU6 | UFQFPN-48 (7×7mm) | ARM Cortex-M4 32-Bit MCU + FPU, 512KB Flash, 128KB RAM | 1 |
| **U3** | MPU-6050 | QFN-24 (4×4mm) | 6-Axis Motion Tracking Sensor (3-Axis Gyro + 3-Axis Accel) | 1 |
| **J1** | 217179-0001 | USB Type-C SMD | Molex 16-Pin USB 2.0 Type-C Receptacle | 1 |
| **J2** | TC2030-NL | Tag-Connect 6-Pin | No-Legs SWD Programming and Debug Connector | 1 |
| **J3** | SM06B-GHS-TB | JST GH 1.25mm 6P | 6-Position Horizontal Auxiliary Expansion Header | 1 |
| **X1** | 24MHz | SMD 3225 | High-Precision System Crystal Resonator (10ppm, 7pF) | 1 |
| **D1** | GREEN | 0402 SMD | Power Status Indicator LED (3.3V Rail) | 1 |
| **D2** | RED | 0402 SMD | Microcontroller Status Indicator LED (PB13) | 1 |
| **D3, D4, D5** | AQ3045-01ETG | SOD-882 | 30kV Automotive Bi-directional TVS ESD Protection Diodes | 3 |
| **C1** | 100nF, 50V | 0402 SMD | Ceramic Input Decoupling Capacitor | 1 |
| **C3, C4** | 22µF | 0805 SMD | Bulk Filtering Capacitors (+5V VBUS & +3.3V LDO Rail) | 2 |
| **C5, C12** | 2.2µF | 0603 SMD | MCU VCAP1 Internal Regulator Filter & IMU Decoupling | 2 |
| **C6, C9, C10, C13, C14, C15, C16, C17, C** | 100nF | 0402 SMD | Power Rail & Reset Decoupling High-Frequency Filter Caps | 9 |
| **C7, C8** | 10pF | 0402 SMD | 24MHz Crystal Oscillator Load Capacitors | 2 |
| **C11** | 2.2nF | 0402 SMD | IMU Charge Pump Output Capacitor (`IMU_CPOUT`) | 1 |
| **R1, R4** | 1kΩ | 0402 SMD | Current-Limiting Resistors for Power and Status LEDs | 2 |
| **R2, R3** | 2.2kΩ | 0402 SMD | I²C Bus Pull-Up Resistors (`IMU_SCL` / `IMU_SDA`) | 2 |
| **R5** | 10kΩ | 0402 SMD | Microcontroller Hardware Reset Pull-Up Resistor (`NRST`) | 1 |
| **R6** | 0Ω | 0402 SMD | Crystal Oscillator Drive Damping / Bypass Resistor | 1 |
| **R7** | 10kΩ | 0402 SMD | Bootloader Configuration Pull-Down Resistor (`BOOT0`) | 1 |
| **R8, R9** | 5.1kΩ | 0402 SMD | USB Type-C Configuration Channel Pull-Downs (CC1 / CC2) | 2 |
| **MH1–MH4** | M3 | 3.2mm NPTH | Mechanical Chassis Mounting Holes (30mm × 30mm Pattern) | 4 |
| **TH1, TH2** | 1.15mm | NPTH | Optical Fabrication and Assembly Tooling Alignment Holes | 2 |

---

## 🏭 Manufacturing Deliverables & Artifacts

All production files are generated in [`manufacturing/`](file:///home/divyansh-rawat/AIPCBDESIGN/emp_projects/07_stm32_imu_module_usbc/manufacturing):
- **Gerber Layers (RS-274X):** Copper, solder masks, silkscreen, paste, edge cuts ([`manufacturing/gerbers/`](file:///home/divyansh-rawat/AIPCBDESIGN/emp_projects/07_stm32_imu_module_usbc/manufacturing/gerbers))
- **Excellon Drill Files:** Plated and non-plated drill hole coordinates ([`manufacturing/gerbers/stm32_imu_module_usbc.drl`](file:///home/divyansh-rawat/AIPCBDESIGN/emp_projects/07_stm32_imu_module_usbc/manufacturing/gerbers/stm32_imu_module_usbc.drl))
- **Fabricator ZIP Archive:** Production archive for PCB fab houses ([`manufacturing/stm32_imu_module_usbc_gerbers.zip`](file:///home/divyansh-rawat/AIPCBDESIGN/emp_projects/07_stm32_imu_module_usbc/manufacturing/stm32_imu_module_usbc_gerbers.zip))
- **Pick-and-Place Position CSV:** Centroid coordinates for automated SMT assembly ([`manufacturing/stm32_imu_module_usbc_pos.csv`](file:///home/divyansh-rawat/AIPCBDESIGN/emp_projects/07_stm32_imu_module_usbc/manufacturing/stm32_imu_module_usbc_pos.csv))
- **Interactive HTML BOM:** Interactive visual assembly inspection tool ([`manufacturing/ibom.html`](file:///home/divyansh-rawat/AIPCBDESIGN/emp_projects/07_stm32_imu_module_usbc/manufacturing/ibom.html))
- **Assembly Documentation PDF:** Production schematic and board drawings ([`manufacturing/stm32_imu_module_usbc.pdf`](file:///home/divyansh-rawat/AIPCBDESIGN/emp_projects/07_stm32_imu_module_usbc/manufacturing/stm32_imu_module_usbc.pdf))
- **Altium-Style 3D Render:** High-resolution perspective render ([`manufacturing/stm32_imu_module_usbc_3d.png`](file:///home/divyansh-rawat/AIPCBDESIGN/emp_projects/07_stm32_imu_module_usbc/manufacturing/stm32_imu_module_usbc_3d.png))

---

## 📐 Mechanical & Layout Constraints
- **Board Outline:** 36.00 mm × 36.00 mm with 3.0 mm radiused corners
- **Layer Count:** 4 Layers (L1: Signal, L2: GND Plane, L3: GND Plane, L4: Signal)
- **Minimum Trace Width:** 0.127 mm (5 mil)
- **Minimum Clearance:** 0.127 mm (5 mil)
- **Via Drill / Diameter:** 0.20 mm drill / 0.40 mm diameter micro-vias
- **Controlled Impedance:** 90 Ω USB differential impedance pair (`USB_D_P` / `USB_D_N`)

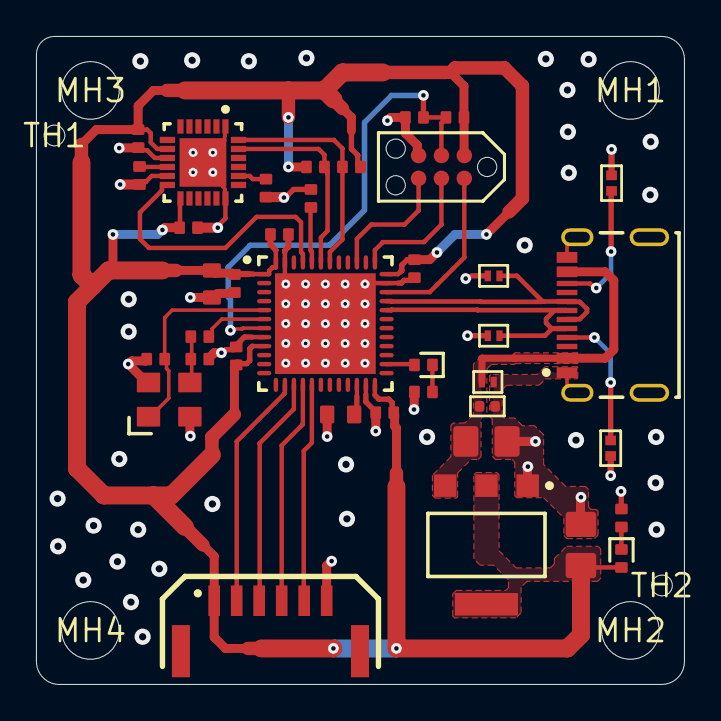
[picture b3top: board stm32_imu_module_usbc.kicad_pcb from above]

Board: 4 copper layers, 36.0 x 36.0 mm, 44 parts (0 on the bottom side), 28 nets.

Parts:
C1: 100nF, 50V; CAPC1005X55N
C2, C6, C9, C10, C13, C14, C15, C16, C17: 100n; CAP_0402
C3, C4: 22u; CAP_0805
C5, C12: 2u2; CAP_0603
C7, C8: 10p; CAP_0402
C11: 2n2; CAP_0402
D1: GREEN; LED_0402_GREEN
D2: RED; LED_0402_RED
D3, D4, D5: AQ3045-01ETG; SOD882
J1: 217179-0001; FP-2171790001-MFG
J2: TC2030-NL; TC2030-NL-FP
J3: SM06B-GHS-TB
MH1, MH2, MH3, MH4: (no value)
R1, R4: 1k; RES_0402
R2, R3: 2k2; RES_0402
R5, R7: 10k; RES_0402
R6: 0R; RES_0402
R8, R9: 5K1; RESC1005X37N
TH1, TH2: (no value)
U1: ams1117; FP-ams1117-IPC_C
U2: STM32F411CEU6; STM-UFQFPN48_L
U3: MPU-6050; IS-QFN-24_V
X1: 24MHz; XTAL_3225

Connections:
+3V3: C2.2, C4.2, C10.2, C12.2, C13.2, C14.2, C15.2, C16.2, C17.2, D1.A, J2.1, J3.1, R2.2, R3.2, R5.2, U1.2, U1.4, U2.1, U2.9, U2.24, U2.36, U2.48, U3.8, U3.13
+5V: C1.2, C3.2, D3.2, J1.A4B9, J1.B4A9, U1.3
GND: C1.1, C2.1, C3.1, C4.1, C5.1, C6.1, C7.1, C8.1, C9.1, C10.1, C11.1, C12.1, C13.1, C14.1, C15.1, C16.1, C17.1, D3.1, D4.1, D5.1, J1.A1B12, J1.B1A12, J1.S1, J1.S2, J1.S3, J1.S4, J2.5, J3.6, R1.1, R4.1, R7.1, R8.1, R9.1, U1.1, U2.8, U2.23, U2.35, U2.47, U2.49, U3.1, U3.9, U3.11, U3.18, U3.25, X1.2, X1.4
IMU_CPOUT: C11.2, U3.20
IMU_INT: U2.45, U3.12
IMU_REGOUT: C9.2, U3.10
IMU_SCL: R2.1, U2.42, U3.24
IMU_SDA: R3.1, U2.43, U3.23
LED_PWR_K: D1.K, R1.2
MCU BOOT0: R7.2, U2.44
MCU_LED_A: D2.A, U2.26
MCU_LED_K: D2.K, R4.2
MCU_NRST: C6.2, J2.3, R5.1, U2.7
MCU_OSC_IN: C7.2, U2.5, X1.1
MCU_OSC_OUT: R6.2, U2.6
MCU_PA4: J3.2, U2.14
MCU_PA5: J3.3, U2.15
MCU_PA6: J3.4, U2.16
MCU_PA7: J3.5, U2.17
MCU_SWCLK: J2.4, U2.37
MCU_SWDIO: J2.2, U2.34
MCU_SWO: J2.6, U2.39
MCU_VCAP1: C5.2, U2.22
NetJ1_A5: J1.A5, R9.2
NetJ1_B5: J1.B5, R8.2
USB_D_N: D4.2, J1.A7, J1.B7, U2.32
USB_D_P: D5.2, J1.A6, J1.B6, U2.33
XTAL_IN: C8.2, R6.1, X1.3

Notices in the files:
EMP_PROJECT/STM32F4 4-Layer Development Board/STM32F4_REV2.kicad_pcb:
Adapted from Phil's Lab STM32F4 Reference (MIT License)
